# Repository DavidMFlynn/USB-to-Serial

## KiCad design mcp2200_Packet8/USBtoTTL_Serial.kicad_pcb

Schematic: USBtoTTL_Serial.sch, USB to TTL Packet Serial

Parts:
C1, C3: 15pf; C_0805_2012Metric_Pad1.15x1.40mm_HandSolder
C2: 4.7uf; C_0805_2012Metric_Pad1.15x1.40mm_HandSolder
C4, C5, C6, C7: 0.1uf; C_0805_2012Metric_Pad1.15x1.40mm_HandSolder
D1, D2: LED; LED_1206_3216Metric_Pad1.42x1.75mm_HandSolder
D3, D4, D5, D6, D7, D8, D9, D10: 1N4148W; D_SOD-123
J1: USB_B; USB_B_OST_USB-B1HSxx_Horizontal
J3: Conn_01x02; Molex_SL_171971-0002_1x02_P2.54mm_Vertical
J4, J5, J6, J7, J8, J9, J10, J11: Conn_01x04; Molex_SL_171971-0004_1x04_P2.54mm_Vertical
R1, R2, R3, R4: 4K7; R_0805_2012Metric_Pad1.15x1.40mm_HandSolder
R5, R6: 0; R_0805_2012Metric_Pad1.15x1.40mm_HandSolder
U1: MCP1700-1202E_SOT23; SOT-23
U2: MCP2200-I-SO; SOIC-20W_7.5x12.8mm_P1.27mm
Y1: 12MHz; Crystal_HC49-4H_Vertical

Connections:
+3V3: C5.1, C6.1, R5.1, U1.2, U2.17 (V_USB)
+5V: C2.1, C4.1, J1.1 (VBUS), R6.2, U1.3
GND: C1.2, C2.2, C3.2, C4.2, C5.2, C6.2, C7.2, J1.4 (GND), J1.5 (Shield), J3.2, J4.2, J5.2, J6.2, J7.2, J8.2, J9.2, J10.2, J11.2, R2.2, R3.2, U1.1, U2.20 (VSS)
unnamed: C1.1, U2.2 (OSC1), Y1.1
unnamed: C3.1, U2.3 (OSC2), Y1.2
unnamed: D1.1 (K), R3.1
unnamed: D1.2 (A), U2.6 (GP6/RxLED)
unnamed: D2.1 (K), R2.1
unnamed: D2.2 (A), U2.5 (GP7/TxLED)
unnamed: D3.1, J4.3
unnamed: D4.1, J5.3
unnamed: D5.1, J6.3
unnamed: D6.1, J7.3
unnamed: D7.1, J8.3
unnamed: D8.1, J9.3
unnamed: D9.1, J10.3
unnamed: D10.1, J11.3
unnamed: J1.2 (D-), U2.18 (D-)
unnamed: J1.3 (D+), U2.19 (D+)
unnamed: J3.1, J4.1, J5.1, J6.1, J7.1, J8.1, J9.1, J10.1, J11.1
unnamed: R1.2, U2.4 (RST)
RX: D3.2, D4.2, D5.2, D6.2, D7.2, D8.2, D9.2, D10.2, R4.2, U2.12 (RX)
TX: J4.4, J5.4, J6.4, J7.4, J8.4, J9.4, J10.4, J11.4, U2.10 (TX)
VDD: C7.1, R1.1, R4.1, R5.2, R6.1, U2.1 (VDD)

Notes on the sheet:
+12V GND
Voltage Select
3V3 5V
+12V GND RX TX

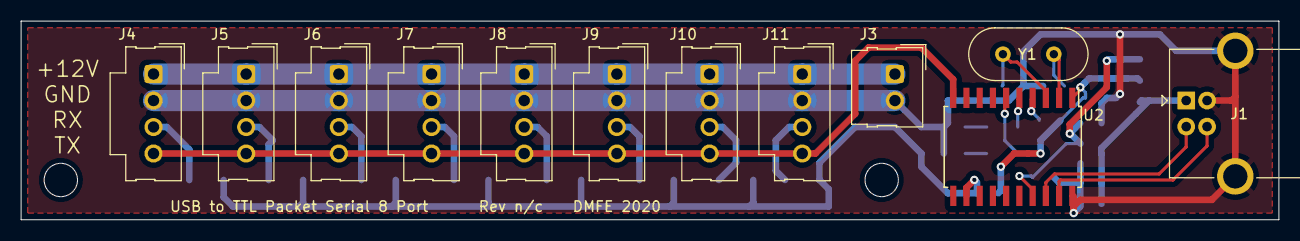
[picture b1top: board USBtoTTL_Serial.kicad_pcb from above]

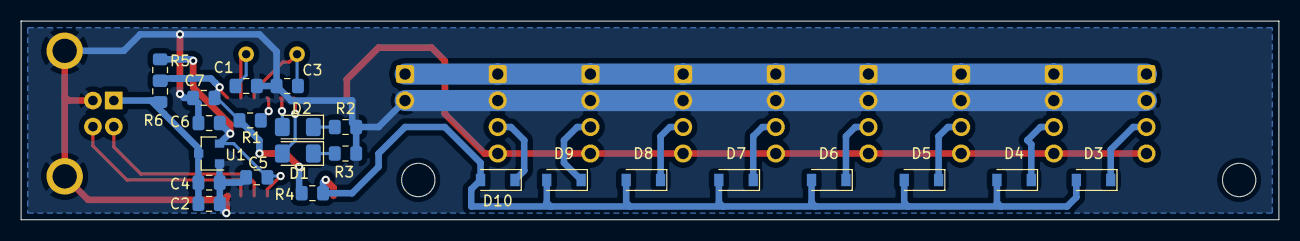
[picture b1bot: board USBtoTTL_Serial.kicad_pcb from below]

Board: 2 copper layers, 120.6 x 19.0 mm, 38 parts (24 on the bottom side), 24 nets.

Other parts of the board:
H1, H2: MountingHole_3.2mm_M3

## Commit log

2020-04-13 removed inv
2020-06-07 Case, 3D printed
